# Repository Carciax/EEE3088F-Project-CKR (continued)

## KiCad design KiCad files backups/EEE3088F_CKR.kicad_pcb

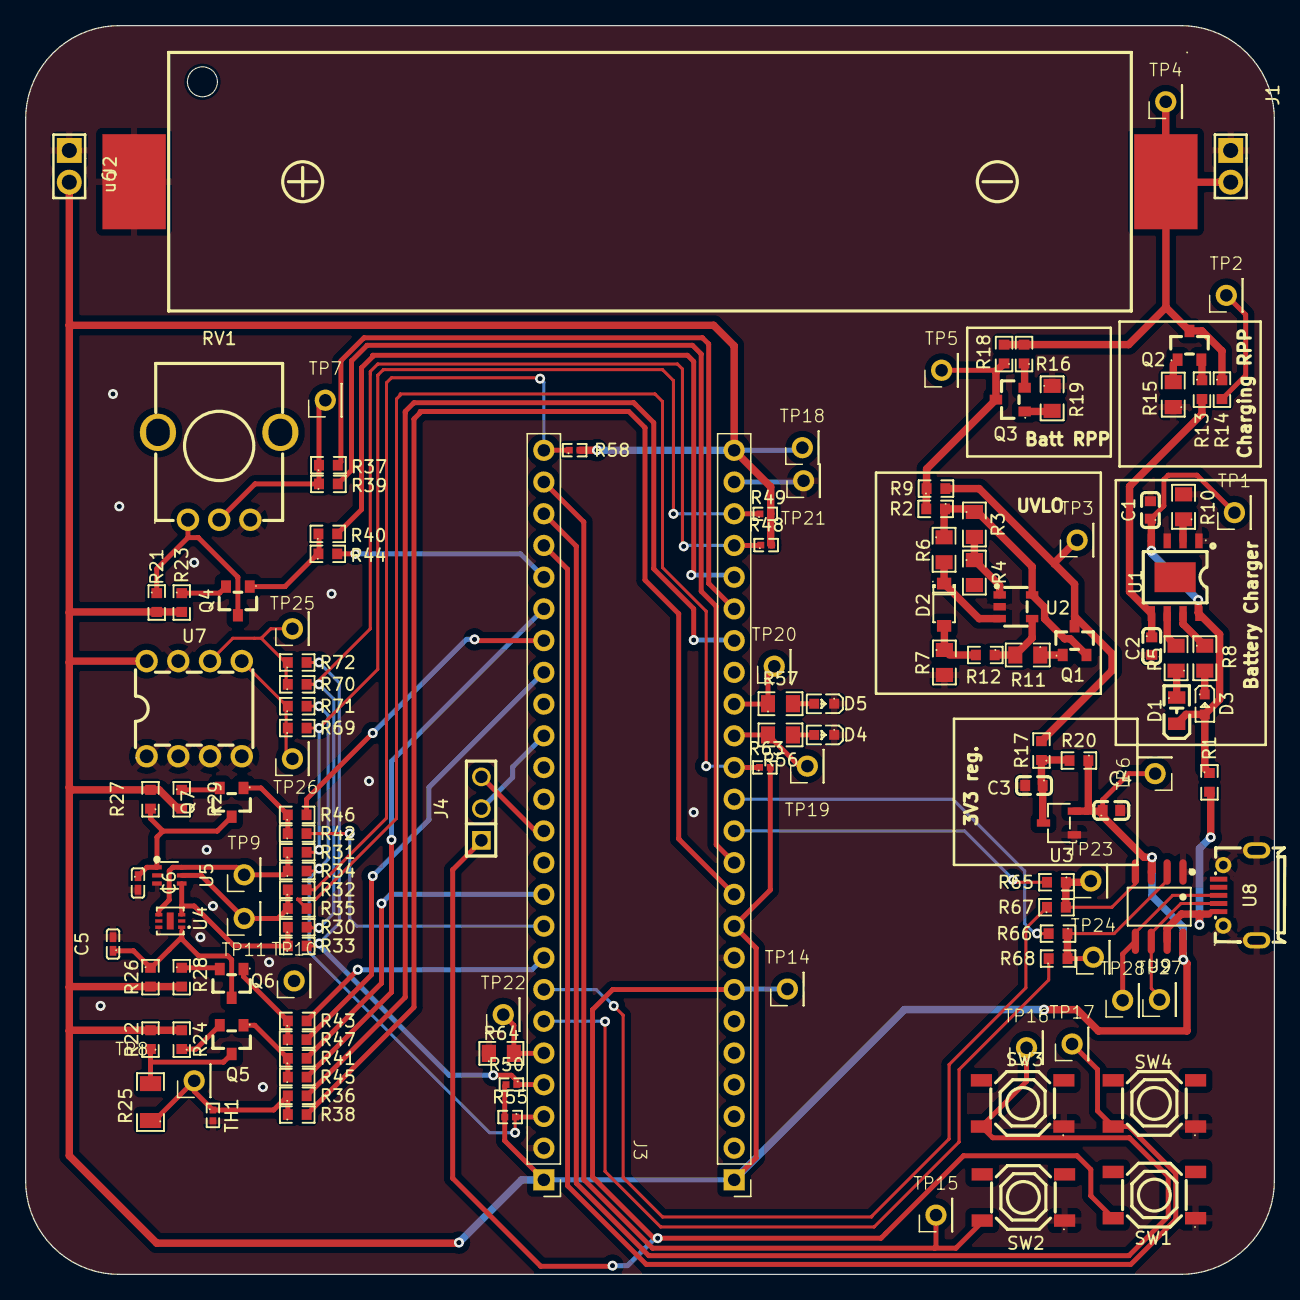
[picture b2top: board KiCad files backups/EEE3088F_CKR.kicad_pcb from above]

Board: 2 copper layers, 100.0 x 100.0 mm, 127 parts (0 on the bottom side), 80 nets.

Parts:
C1, C2, C3, C4: 10uf; C0603
C5: 100n; C0402_NEW
C6: 1u; C0402
D1: LED Green; LED0805-R-RD
D2: zener diode; SOD-123_L2.8-W1.8-LS3.7-RD
D3: LED RED; LED0603-RD
D4, D5: LED; LED0603-RD
J1, J2: Conn_01x02_Pin; HDR-TH_2P-P2.54-V-M
J3: STM32F051C6_female_header
J4: Debugger; HDR-TH_3P-P2.54_CS-1165SDIG
Q1, Q2, Q3, Q4, Q5, Q6, Q7: AO3401A; SOT-23_L2.9-W1.3-P1.90-LS2.4-BR
R1, R2, R9, R13, R14, R16, R17, R18, R20, R21, R22, R23, R24, R26, R27, R28, R29, R30, R31, R32, R33, R34, R35, R36, R37, R38, R39, R40, R41, R42, R43, R44, R45, R46, R47, R65, R66, R67, R68, R69, R70, R71, R72: 0; R0603
R3, R11: R1M; R0805
R4: R2M; R0805
R5, R8, R10, R15, R19, R56, R57: 1.2k; R0805
R6: 27.5k; R0805
R7, R64: 10k; R0805
R12: R3M; R0603
R25: 100k; R1206
R48, R49, R50, R55: 3.9k; R0402
R58, R63: 8.2k; R0402
RV1: R_Potentiometer; RES-ADJ-TH_RK09K1130AJ3
SW1: Reset switch; SW-SMD_4P-L5.1-W5.1-P3.70-LS6.5-TL-2
SW2, SW3, SW4: switch; SW-SMD_4P-L5.1-W5.1-P3.70-LS6.5-TL-2
TH1: Thermistor; R0402
TP1: 5v; Testpoint_2.54mm
TP2: battery charger; Testpoint_2.54mm
TP3: UVLO; Testpoint_2.54mm
TP4: +battery out; Testpoint_2.54mm
TP5: reverse polarity; Testpoint_2.54mm
TP6: 3.3v out; Testpoint_2.54mm
TP7: Pot ADC; Testpoint_2.54mm
TP8: Therm ADC; Testpoint_2.54mm
TP9: Light SDA; Testpoint_2.54mm
TP10: Light SCL; Testpoint_2.54mm
TP11: Light Interrupt; Testpoint_2.54mm
TP14: NSRT; Testpoint_2.54mm
TP15: Switch1; Testpoint_2.54mm
TP16: Switch2; Testpoint_2.54mm
TP17: Switch3; Testpoint_2.54mm
TP18: STM32 3V3; Testpoint_2.54mm
TP19: STM32 LED1; Testpoint_2.54mm
TP20: STM32 LED2; Testpoint_2.54mm
TP21: STM32 GND; Testpoint_2.54mm
TP22: STM32 BOOT0; Testpoint_2.54mm
TP23: STM32 Tx; Testpoint_2.54mm
TP24: STM32 Rx; Testpoint_2.54mm
TP25: EEPROM SDA; Testpoint_2.54mm
TP26: EEPROM SCL; Testpoint_2.54mm
TP27: USB D-; Testpoint_2.54mm
TP28: USB D+; Testpoint_2.54mm
U1: Battery Charger; ESOP-8_L4.9-W3.9-P1.27-LS6.0-BL-EP
U2: LMV321; SOT-23-5_L3.0-W1.7-P0.95-LS2.8-BR
U3: XC6206PxxxMR; SOT-23-3_L2.9-W1.6-P1.90-LS2.8-BR
U4: GXHTC3; DFN-6_L2.0-W2.0-P0.50-BL-EP
U5: LTR-303ALS-01; SOT-363_L2.0-W1.3-P0.65-LS2.1-BL
U7: 24LC256; PDIP-8_L9.3-W6.4-P2.54-LS7.6-BL
U8: usb; MICRO-USB-SMD_MICROXNJ
U9: HT42B534-2; SOIC-8_L4.9-W3.9-P1.27-LS6.0-BL
u6: battery holder; BATTERY-SMD_18650-1S-L77.1-W20.7-1

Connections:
+3V3: C4.1, J2.2, J3.1 (_VBAT), J3.9 (_VDDA), J3.24 (_VDD), J3.48 (VDD_), R20.1, R21.2, R22.2, R23.2, R24.2, R26.2, R27.2, R28.2, R29.2, R48.2, R49.2, R50.2, R55.2, R58.2, R63.2, TP6.1, TP18.1, U3.2 (VO), U7.8 (VCC), U9.3 (VDDIO), U9.8 (V330)
+5V: R1.2, U8.1 (VBUS), U9.7 (VDD)
/Microcontroller/BOOT0: J3.44 (BOOT0_), R64.2, TP22.1
/Microcontroller/INT_1: J3.25 (PB12_), R32.2, R58.1
/Microcontroller/INT_2: J3.14 (_PA4), R35.2, R63.1
/Microcontroller/LED1_1: J3.15 (_PA5), R56.1, TP19.1
/Microcontroller/LED2_1: J3.16 (_PA6), R57.1, TP20.1
/Microcontroller/Lght_P_1: J3.40 (PB4_), R42.2
/Microcontroller/Lght_P_2: J3.31 (PA10_), R46.2
/Microcontroller/Light_powerenable: Q7.1 (G), R42.1, R46.1
/Microcontroller/NSRT: J3.7 (_NSRT), J4.1, SW1.2, TP14.1
/Microcontroller/POT_1: J3.19 (_PB1), R37.2
/Microcontroller/POT_2: J3.11 (_PA1), R39.2
/Microcontroller/POT_P_1: J3.20 (_PB2), R40.2
/Microcontroller/POT_P_2: J3.29 (PA8_), R44.2
/Microcontroller/Potentiometer_powerenable: Q4.1 (G), R40.1, R44.1
/Microcontroller/Potentiometer_signal: R37.1, R39.1, RV1.2, TP7.1
/Microcontroller/Rx: R66.1, R68.2, TP24.1, U9.2 (Tx)
/Microcontroller/Rx_1: J3.43 (PB7_), R68.1
/Microcontroller/Rx_2: J3.13 (_PA3), R66.2
/Microcontroller/SCL_1: J3.21 (_PB10), R30.2, R48.1, R70.2
/Microcontroller/SCL_2: J3.45 (PB8_), R33.2, R50.1, R72.2
/Microcontroller/SDA_1: J3.22 (_PB11), R31.2, R49.1, R69.2
/Microcontroller/SDA_2: J3.46 (PB9_), R34.2, R55.1, R71.2
/Microcontroller/SW1: J3.26 (PB13_), SW2.2, TP15.1
/Microcontroller/SW2: J3.27 (PB14_), SW3.2, TP16.1
/Microcontroller/SW3: J3.28 (PB15_), SW4.2, TP17.1
/Microcontroller/SWCLK: J3.37 (PA14_), J4.3
/Microcontroller/SWDIO: J3.34 (PA13_), J4.2
/Microcontroller/THM_1: J3.18 (_PB0), R36.2
/Microcontroller/THM_2: J3.10 (_PA0), R38.2
/Microcontroller/THM_P_1: J3.39 (PB3_), R41.2
/Microcontroller/THM_P_2: J3.30 (PA9_), R45.2
/Microcontroller/TeHu_P_1: J3.41 (PB5_), R43.2
/Microcontroller/TeHu_P_2: J3.32 (PA11_), R47.2
/Microcontroller/TemperatureHumidity_powerenable: Q6.1 (G), R43.1, R47.1
/Microcontroller/Thermistor_powerenable: Q5.1 (G), R41.1, R45.1
/Microcontroller/Thermistor_signal: R25.1, R36.1, R38.1, TH1.1, TP8.1
/Microcontroller/Tx: R65.1, R67.2, TP23.1, U9.4 (Rx)
/Microcontroller/Tx_1: J3.42 (PB6_), R67.1
/Microcontroller/Tx_2: J3.12 (_PA2), R65.2
/Power/3.3V UVLO/polarity protector: Q1.3 (D), R9.2, R17.2, TP3.1
/Power/polarity protected battery voltage: Q3.3 (D), R2.2, R9.1, R18.1, TP5.1
/Sensors/Light_SCL: R30.1, R33.1, TP10.1, U4.3 (SCL), U5.4 (SCL)
/Sensors/Light_SDA: R31.1, R34.1, TP9.1, U4.4 (SDA), U5.6 (SDA)
/Sensors/Light_interrupt: R32.1, R35.1, TP11.1, U5.5 (INT)
GND: C1.2, C2.2, C3.2, C4.2, C5.2, C6.2, D4.1 (K), D5.1 (K), J1.1, J2.1, J3.8 (_VSSA), J3.23 (_VSS), J3.47 (VSS_), R4.2, R7.2, R10.2, R15.1, R19.1, R64.1, RV1.3, SW1.1, SW2.1, SW3.1, SW4.1, TH1.2, TP21.1, U1.1 (TEMP), U1.3 (GND), U2.2 (V-), U3.1 (GND), U4.6 (GND), U5.3 (GND), U7.1 (A0), U7.2 (A1), U7.3 (A2), U7.4 (GND), U7.7 (WP), U8.5 (GND), U8.6 (SH1), U8.7 (SH2), U8.8 (SH3), U8.9 (SH4), U9.1 (GND), u6.2 (-)
unnamed: C3.1, R17.1, R20.2, U3.3 (VI)
unnamed: Q1.2 (S), R2.1, R3.1, R6.1, U2.5 (V+)
unnamed: C5.1, Q6.3 (D), R26.1, U4.1 (VDD)
unnamed: C6.1, Q7.3 (D), R27.1, U5.1 (VDD)
unnamed: C1.1, D1.2 (A), D3.2 (A), R1.1, TP1.1, U1.4 (Vcc), U1.8 (CE)
unnamed: D1.1 (K), R5.1
unnamed: D2.2, R7.1, R12.2
unnamed: D3.1 (K), R8.2
unnamed: D4.2 (A), R56.2
unnamed: D5.2 (A), R57.2
unnamed: J1.2, Q2.3 (D), R14.1, R16.2, R18.2, TP4.1, u6.1 (+)
unnamed: Q1.1 (G), R11.1
unnamed: Q2.1 (G), R15.2
unnamed: Q2.2 (S), R13.1
unnamed: Q3.1 (G), R19.2
unnamed: Q3.2 (S), R16.1
unnamed: Q4.3 (D), R21.1, RV1.1
unnamed: Q4.2 (S), R23.1
unnamed: Q5.3 (D), R22.1, R25.2
unnamed: Q5.2 (S), R24.1
unnamed: Q6.2 (S), R28.1
unnamed: Q7.2 (S), R29.1
unnamed: R11.2, R12.1, U2.4
unnamed: C2.1, R13.2, R14.2, TP2.1, U1.5 (BAT)
unnamed: R8.1, U1.7 (CHRG)
unnamed: R10.1, U1.2 (PROG)
unnamed: R5.2, U1.6 (STDBY#)
unnamed: R3.2, R4.1, U2.1 (+)
unnamed: D2.1, R6.2, U2.3 (-)
unnamed: R70.1, R72.1, TP25.1, U7.6 (SCL)
unnamed: R69.1, R71.1, TP26.1, U7.5 (SDA)
unnamed: TP28.1, U8.3 (D+), U9.5 (D+)
unnamed: TP27.1, U8.2 (D-), U9.6 (D-)

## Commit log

2023-02-21 Added Proposal doc
2023-02-21 Added student numbers to README
2023-02-24 Added budgeting spreadsheet
2023-02-24 Written Q1 in proposal
2023-02-24 Added github link
2023-02-24 added users and requirements excel doc
2023-02-24 Finished proposal
2023-02-24 updated block diagram
2023-02-26 Added pdf of proposal
2023-02-26 Added structure
2023-03-03 added
2023-03-03 updated sheet heirachy
2023-03-03 microcontroller added
2023-03-03 added stm32 datasheet
2023-03-04 changed to kicad7
2023-03-04 added microcontroller, power, and sensors
2023-03-05 kian added power subsistem week 3 Q1.1
2023-03-05 kian made som changes to the scmatices for power an added a libaery called power componentes
2023-03-05 kian made som changes to the scmatices
2023-03-05 I think I finally got the renaming of folders right'
2023-03-05 started Week 3 Q3 answers
2023-03-05 finale scamatic for today
2023-03-05 Updated design proposal Q3 and added sensor datasheets
2023-03-05 Q1.2 done
2023-03-05 added Q3 sensors details, started sensors schematic, updated sym-lib-table to reflect renamed files from previous commit
2023-03-05 updated Q3 sensors doc
2023-03-05 added final word document for Q1
2023-03-05 Updated digital sensor in sensors schematic
2023-03-05 fixed up spelling errors
2023-03-05 minor changes to schematic, added sensor sheet to BOM
2023-03-05 not 100% sure but I probably updated some stuff
2023-03-05 updated BOM with microcontoller
2023-03-05 added microcontroller requirements
2023-03-05 added Q2.3
2023-03-05 Added thermister stuff
2023-03-05 same as above
2023-03-05 renamed BOM file
2023-03-05 added thermister stuff to BOM
2023-03-06 updated Q3 sensors and added answers for design review task
2023-03-06 added Rob's Design review notes
2023-03-06 added pot and 2nd I2C pin to microcontroller schematic
2023-03-06 Added KiCad backups
2023-03-06 some stuff
2023-03-06 updated for uController
2023-03-06 added assign. 2 submission
2023-03-07 reordered git
2023-03-07 changed battery to DNP
2023-03-07 added EEPROM
2023-03-07 added switches
2023-03-07 added microcontoller female header part
2023-03-07 changed such that only headers are placed on board
2023-03-07 added heirachals and connected subsheets
2023-03-09 added doc for power anseres
2023-03-10 added USB to USART datasheet
2023-03-10 added USB to UART connector and made a dedicated USB sheet
2023-03-11 Added sheet notes and initial design template, reordered microcontoller subsheet and add microntoller subsheet notes
2023-03-11 some changes to power
2023-03-11 power circit done
2023-03-11 bom power add
2023-03-13 started adding temperature & humidity sensor to sensors schematic, small changes to rob week 4 doc
2023-03-13 same as previous
2023-03-13 power retry
2023-03-13 power bom'
2023-03-13 power bom
2023-03-13 added failure mitigations and updated BOM
2023-03-13 changes to sensor schematic :
2023-03-13 updated sensor and microcontroller schematics
2023-03-13 minor changes
2023-03-13 added week 4 design review notes to rob's section week 4
2023-03-14 power scmatic added
2023-03-14 power scamatic
2023-03-14 edited circuit diagram in template design
2023-03-14 Added sensor info to week 4 doc
2023-03-14 git commit
2023-03-14 git bom add feilds
2023-03-14 git Bom power
2023-03-14 finalised initial template design
2023-03-18 power scamatic updated
2023-03-18 added test point
2023-03-18 power Updated added test points and some 0 ohm resistors as well as trying to fix off-grid problem
2023-03-19 sensors schematic changes, net label name changes
2023-03-19 added test points to sensor schem
2023-03-19 Added testpoint and changed headers to 0Ωs
2023-03-19 Added more test points
2023-03-19 updated 0Ω to be DNP
2023-03-19 changed a bunch of net labels, changed some uc schem stuff
2023-03-19 power final chang
2023-03-19 updated net labelling scheme on schematic, changed some port connections on microcontroller
2023-03-20 ran ERCs and fixed the errors
2023-03-20 bom updated and test labes renamed
2023-03-20 liabary added
2023-03-20 lots of suf for pcb diseng
2023-03-20 footprint added
2023-03-20 made STM32 footprint
2023-03-20 gerber power changed
2023-03-20 lots of PCB stuff
2023-03-21 the PCB suffered - wired up the micro controller
2023-03-21 double checking my push
2023-03-21 a few random vias
2023-03-21 bom added
2023-03-21 power scamtic wire added
2023-03-21 week 5 right up added
2023-03-21 week 5 writeup and a lot of changes to PCB design
2023-03-22 any missing files from week 5 submission
2023-03-23 added peer review folder
2023-03-24 cleaned up git order
2023-03-24 added MCU stuff to review
2023-03-27 power peer review done
2023-03-27 power peer review added
2023-03-27 Rob's input to peer review doc
2023-03-31 powwer 5v line seperation
2023-03-31 Removed extra 0ohms, added microcontroller male header
2023-04-01 power cirucat chang
2023-04-01 Significant schematic changes
2023-04-02 any residual changes from previous commit
2023-04-02 Corrected all part numbers and small schematic changes
2023-04-02 small changes
2023-04-02 Final schematic changes and start board design
2023-04-03 literally just added one 0ohm resistor
2023-04-03 Lots of PCB design
2023-04-04 finally finished PCB design
2023-04-12 made backup of PCB layout
2023-04-13 Added new UVLO component schem
2023-04-13 updated UVLO
2023-04-13 small schem changes
2023-04-13 maybe there are some changes?
2023-04-14 kian chang UVLO in gRB
2023-04-14 made final production files
2023-04-14 residual changes
2023-04-14 cleaned up file directory a bit
2023-05-11 added STM cube setup
2023-05-13 basic code setup completed, added ADC readouts
2023-05-13 Updating readme.md
2023-05-13 read me updated
2023-05-13 small code changes
2023-05-13 Added CONTRIBUTING.md
2023-05-13 reed me added to
2023-05-13 Added code structure doc
2023-05-13 Updated tech documentation stuff
2023-05-14 Create LICENSE
    added mit licens
2023-05-14 Update README.md
    added licens agrement
2023-05-14 code documentation
2023-05-14 changed some filenames
2023-05-14 chagned filename
2023-05-14 created submission doc for week 12 assignment
2023-05-19 interpretation code
2023-05-19 Added PCB code
